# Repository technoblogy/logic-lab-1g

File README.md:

# Logic Lab 1G

A board that provides 12 logic gates that you can interconnect with patch cables to make a variety of different logic circuits. This version is implemented with 12 individual logic gates.

For more information see <http://www.technoblogy.com/show?4ODG>.

Alternatively see [Logic Lab](https://github.com/technoblogy/logic-lab) which is functionally identical, but implemented using an AVR microcontroller.

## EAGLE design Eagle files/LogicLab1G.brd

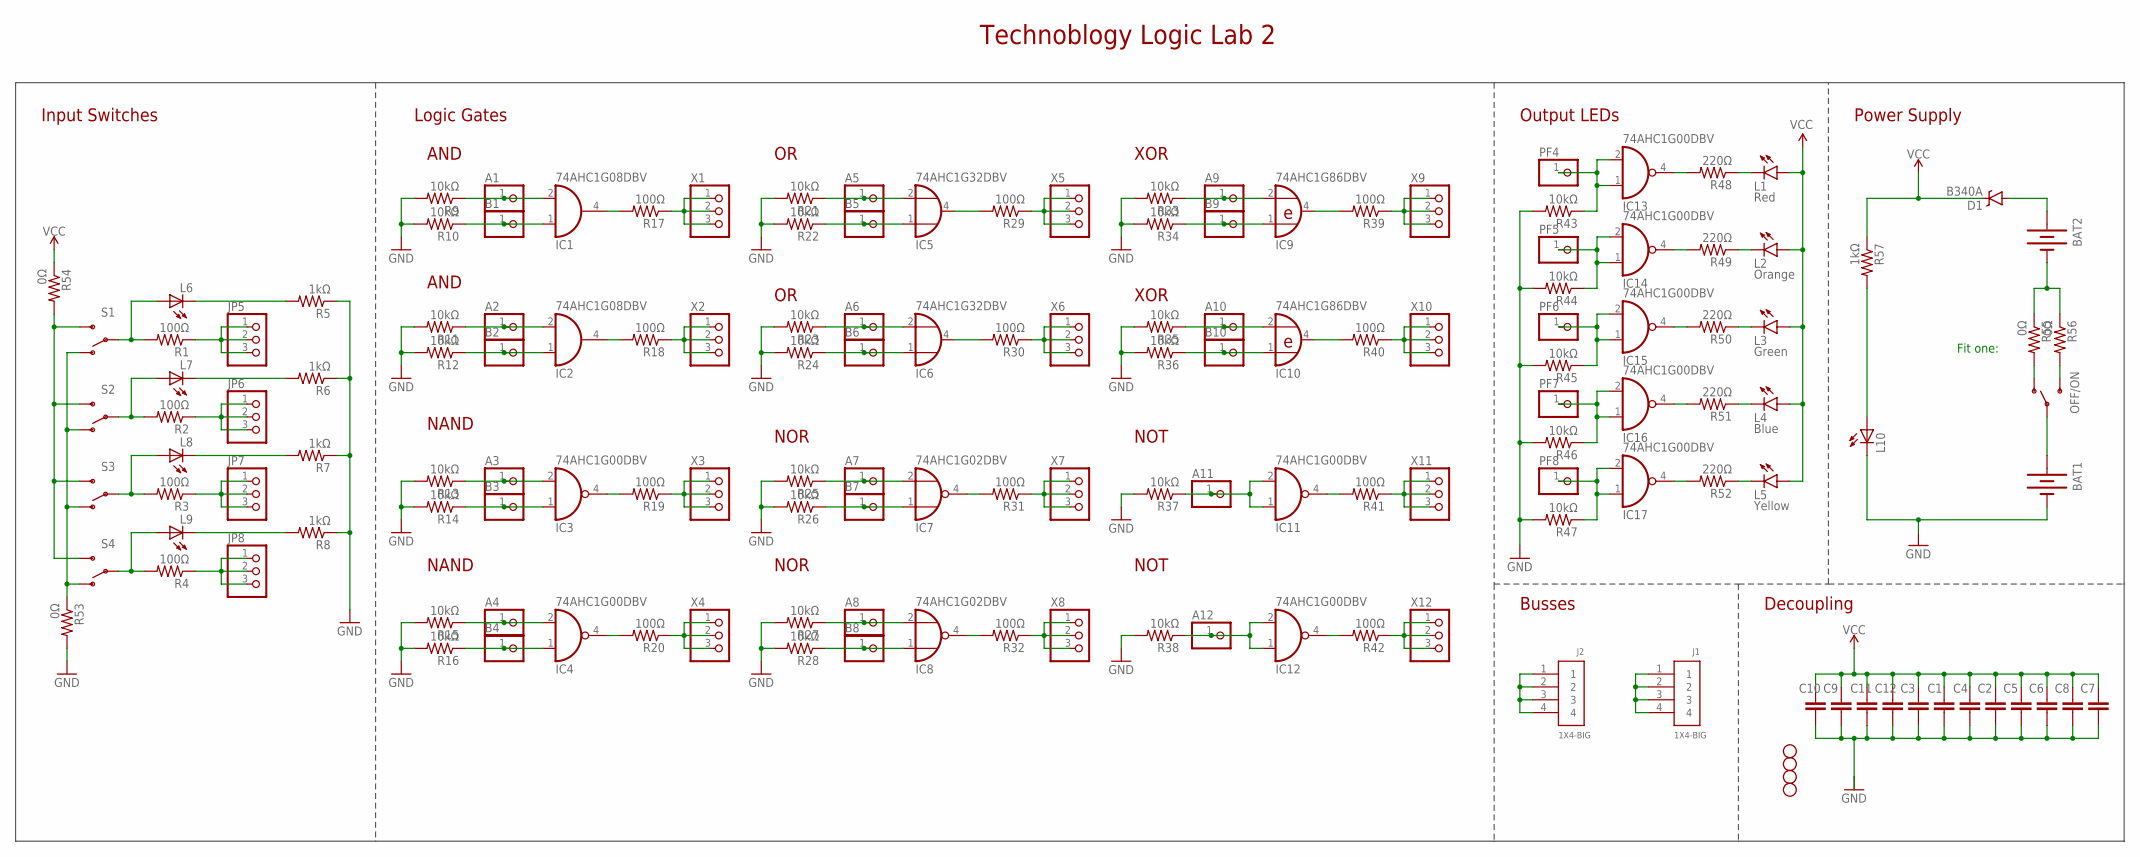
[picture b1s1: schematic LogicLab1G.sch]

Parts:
A1, A2, A3, A4, A5, A6, A7, A8, A9, A10, A11, A12: PINHD-1X1; 1X01
B1, B2, B3, B4, B5, B6, B7, B8, B9, B10: PINHD-1X1; 1X01
BAT1, BAT2: BATTERYAAA-KIT; BATTERY-AAA-KIT
C1, C2, C3, C5, C6, C7, C8, C9, C10, C12: 100n; 0805
C4, C11: 10uF; 0805
D1: B340A; SMA-DIODE
IC1, IC2: 74AHC1G08DBV; SOT23-5
IC3, IC4, IC11, IC12, IC13, IC14, IC15, IC16, IC17: 74AHC1G00DBV; SOT23-5
IC5, IC6: 74AHC1G32DBV; SOT23-5
IC7, IC8: 74AHC1G02DBV; SOT23-5
IC9, IC10: 74AHC1G86DBV; SOT23-5
J1, J2: 1X4-BIG; 1X04-BIG
JP1, JP2, JP3, JP4: STAND-OFF
JP5, JP6, JP7, JP8: PINHD-1X3; 1X03
L1: Red; LED5MM
L2: Orange; LED5MM
L3: Green; LED5MM
L4: Blue; LED5MM
L5: Yellow; LED5MM
L6, L7, L8, L9, L10: LEDCHIPLED_0805; CHIPLED_0805
OFF/ON: SWITCH-SPDTKIT; SWITCH-SPDT_KIT
PF4, PF5, PF6, PF7, PF8: PINHD-1X1; 1X01
R1, R2, R3, R4, R17, R18, R19, R20, R29, R30, R31, R32, R39, R40, R41, R42: 100Ω; 0805
R5, R6, R7, R8, R57: 1kΩ; 0805
R9, R10, R11, R12, R13, R14, R15, R16, R21, R22, R23, R24, R25, R26, R27, R28, R33, R34, R35, R36, R37, R38, R43, R44, R45, R46, R47: 10kΩ; 0805
R48, R49, R50, R51, R52: 220Ω; 0805
R53, R54, R55, R56: 0Ω; 0805
S1, S2, S3, S4: SWITCH-SPDTKIT; SWITCH-SPDT_KIT
X1, X2, X3, X4, X5, X6, X7, X8, X9, X10, X11, X12: PINHD-1X3; 1X03

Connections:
BOTTOMS: R53.1, S1.1 (O), S2.1 (O), S3.1 (O), S4.1 (O)
GND: BAT1.GND@1 (-), C1.2, C2.2, C3.2, C4.2, C5.2, C6.2, C7.2, C8.2, C9.2, C10.2, C11.2, C12.2, IC1.3 (GND), IC2.3 (GND), IC3.3 (GND), IC4.3 (GND), IC5.3 (GND), IC6.3 (GND), IC7.3 (GND), IC8.3 (GND), IC9.3 (GND), IC10.3 (GND), IC11.3 (GND), IC12.3 (GND), IC13.3 (GND), IC14.3 (GND), IC15.3 (GND), IC16.3 (GND), IC17.3 (GND), L10.C, R5.1, R6.1, R7.1, R8.1, R9.2, R10.2, R11.2, R12.2, R13.2, R14.2, R15.2, R16.2, R21.2, R22.2, R23.2, R24.2, R25.2, R26.2, R27.2, R28.2, R33.2, R34.2, R35.2, R36.2, R37.2, R38.2, R43.2, R44.2, R45.2, R46.2, R47.2, R53.2
unnamed: A9.1, IC9.2 (I1), R33.1
unnamed: R30.1, X6.1, X6.2, X6.3
unnamed: R29.1, X5.1, X5.2, X5.3
unnamed: B4.1, IC4.1 (I0), R16.1
unnamed: IC13.4 (O), R48.2
unnamed: IC14.4 (O), R49.2
unnamed: IC15.4 (O), R50.2
unnamed: BAT1.PWR@1 (+), OFF/ON.2
unnamed: B10.1, IC10.1 (I0), R36.1
unnamed: IC16.4 (O), R51.2
unnamed: A4.1, IC4.2 (I1), R15.1
unnamed: IC17.4 (O), R52.2
unnamed: BAT2.PWR@1 (+), D1.A
unnamed: R39.1, X9.1, X9.2, X9.3
unnamed: IC2.4 (O), R18.2
unnamed: OFF/ON.1 (O), R55.2
unnamed: R40.1, X10.1, X10.2, X10.3
unnamed: A1.1, IC1.2 (I1), R9.1
unnamed: IC5.4 (O), R29.2
unnamed: BAT2.GND@1 (-), R55.1, R56.1
unnamed: L1.K (C), R48.1
unnamed: B3.1, IC3.1 (I0), R14.1
unnamed: B1.1, IC1.1 (I0), R10.1
unnamed: B7.1, IC7.1 (I0), R26.1
unnamed: B9.1, IC9.1 (I0), R34.1
unnamed: R17.1, X1.1, X1.2, X1.3
unnamed: R41.1, X11.1, X11.2, X11.3
unnamed: OFF/ON.3 (S), R56.2
unnamed: R18.1, X2.1, X2.2, X2.3
unnamed: B2.1, IC2.1 (I0), R12.1
unnamed: A10.1, IC10.2 (I1), R35.1
unnamed: R42.1, X12.1, X12.2, X12.3
unnamed: L6.A, R1.2, S1.2
unnamed: R19.1, X3.1, X3.2, X3.3
unnamed: A8.1, IC8.2 (I1), R27.1
unnamed: R31.1, X7.1, X7.2, X7.3
unnamed: B5.1, IC5.1 (I0), R22.1
unnamed: L7.A, R2.2, S2.2
unnamed: A5.1, IC5.2 (I1), R21.1
unnamed: IC3.4 (O), R19.2
unnamed: IC9.4 (O), R39.2
unnamed: IC10.4 (O), R40.2
unnamed: IC12.4 (O), R42.2
unnamed: IC11.4 (O), R41.2
unnamed: R32.1, X8.1, X8.2, X8.3
unnamed: A11.1, IC11.1 (I0), IC11.2 (I1), R37.1
unnamed: A12.1, IC12.1 (I0), IC12.2 (I1), R38.1
unnamed: L2.K (C), R49.1
unnamed: IC6.4 (O), R30.2
unnamed: L8.A, R3.2, S3.2
unnamed: L9.A, R4.2, S4.2
unnamed: IC4.4 (O), R20.2
unnamed: R20.1, X4.1, X4.2, X4.3
unnamed: L3.K (C), R50.1
unnamed: L4.K (C), R51.1
unnamed: L5.K (C), R52.1
unnamed: IC13.1 (I0), IC13.2 (I1), PF4.1, R43.1
unnamed: IC14.1 (I0), IC14.2 (I1), PF5.1, R44.1
unnamed: JP8.1, JP8.2, JP8.3, R4.1
unnamed: JP7.1, JP7.2, JP7.3, R3.1
unnamed: L10.A, R57.2
unnamed: J2.1, J2.2, J2.3, J2.4
unnamed: JP6.1, JP6.2, JP6.3, R2.1
unnamed: L9.C, R8.2
unnamed: L8.C, R7.2
unnamed: JP5.1, JP5.2, JP5.3, R1.1
unnamed: L6.C, R5.2
unnamed: L7.C, R6.2
unnamed: B8.1, IC8.1 (I0), R28.1
unnamed: J1.1, J1.2, J1.3, J1.4
unnamed: A6.1, IC6.2 (I1), R23.1
unnamed: IC15.1 (I0), IC15.2 (I1), PF6.1, R45.1
unnamed: B6.1, IC6.1 (I0), R24.1
unnamed: A7.1, IC7.2 (I1), R25.1
unnamed: A3.1, IC3.2 (I1), R13.1
unnamed: A2.1, IC2.2 (I1), R11.1
unnamed: IC8.4 (O), R32.2
unnamed: IC7.4 (O), R31.2
unnamed: IC16.1 (I0), IC16.2 (I1), PF7.1, R46.1
unnamed: IC17.1 (I0), IC17.2 (I1), PF8.1, R47.1
unnamed: IC1.4 (O), R17.2
TOPS: R54.2, S1.3 (S), S2.3 (S), S3.3 (S), S4.3 (S)
VCC: C1.1, C2.1, C3.1, C4.1, C5.1, C6.1, C7.1, C8.1, C9.1, C10.1, C11.1, C12.1, D1.C, IC1.5 (VCC), IC2.5 (VCC), IC3.5 (VCC), IC4.5 (VCC), IC5.5 (VCC), IC6.5 (VCC), IC7.5 (VCC), IC8.5 (VCC), IC9.5 (VCC), IC10.5 (VCC), IC11.5 (VCC), IC12.5 (VCC), IC13.5 (VCC), IC14.5 (VCC), IC15.5 (VCC), IC16.5 (VCC), IC17.5 (VCC), L1.A, L2.A, L3.A, L4.A, L5.A, R54.1, R57.1

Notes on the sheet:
Technoblogy Logic Lab 2
Input Switches
Logic Gates
Output LEDs
Power Supply
AND
Busses
NAND
NOR
NOT
XOR
Decoupling
Fit one:

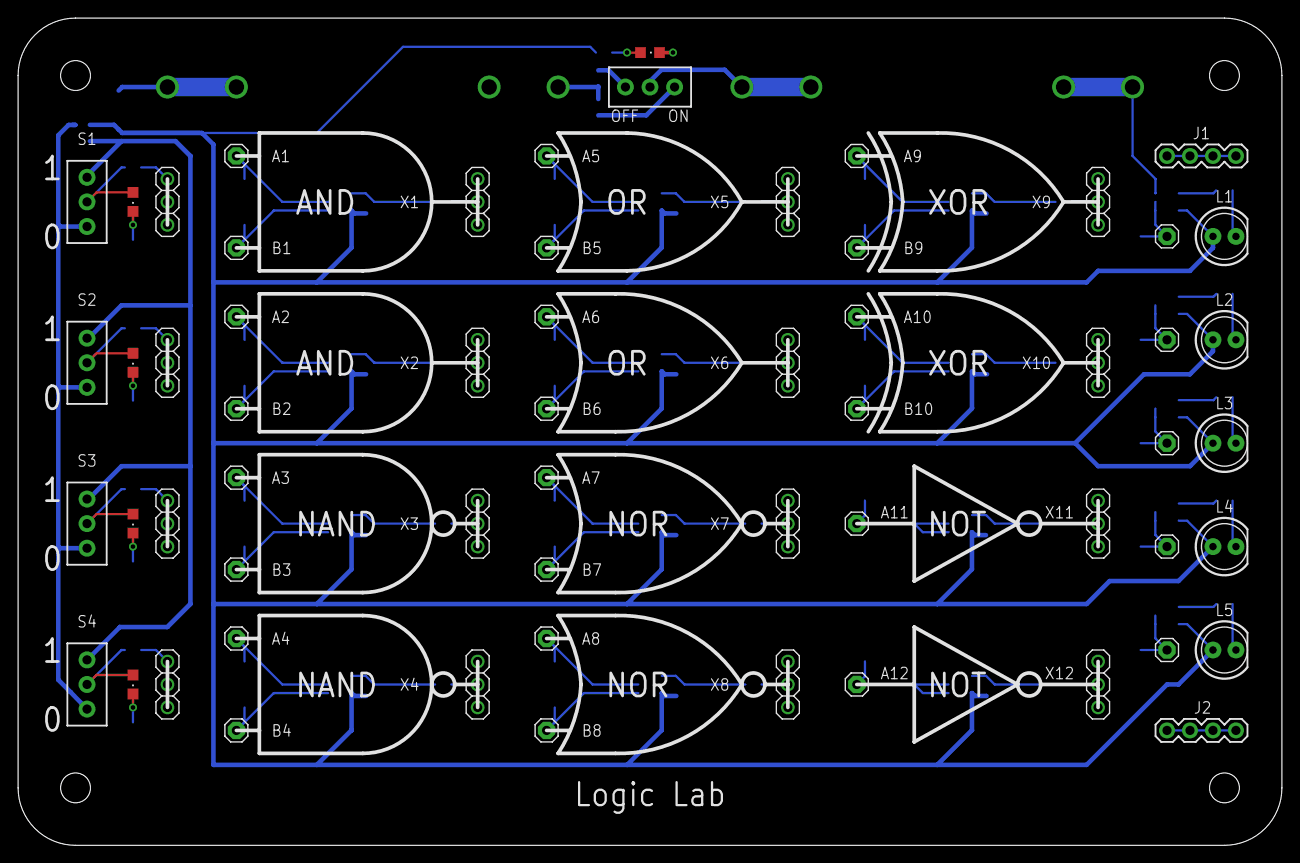
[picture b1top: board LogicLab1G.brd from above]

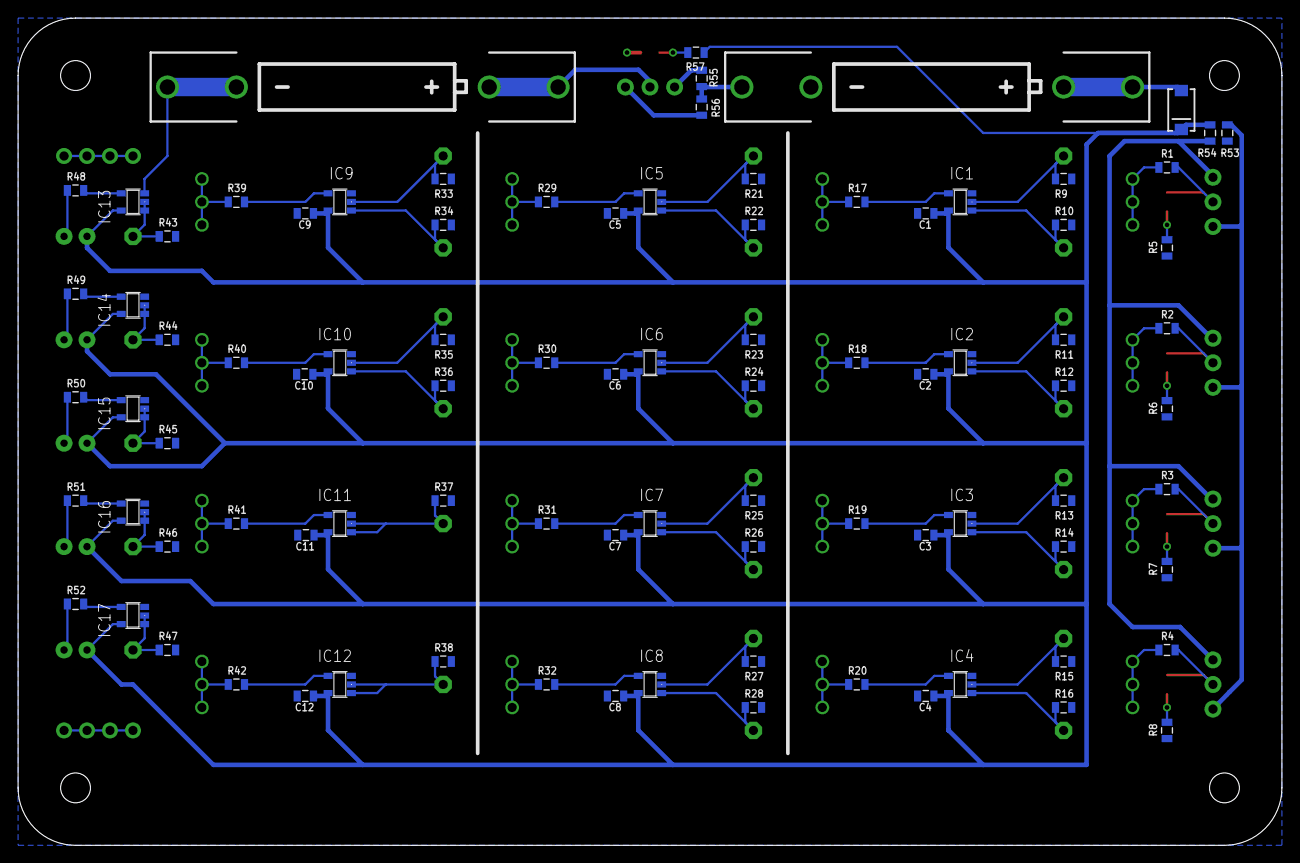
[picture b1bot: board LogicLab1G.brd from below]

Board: 2 copper layers, 139.7 x 91.4 mm, 153 parts (89 on the bottom side), 85 nets.

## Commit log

2024-05-05 Version 1 - 5th May 2024
2024-06-17 Version 1a - 17th June 2024
    Corrected the part numbers of the logic gates.
2026-02-28 CC BY-SA 4.0

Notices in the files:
parts and their libraries:
SparkFun-Electromechanical: Licensing: Creative Commons ShareAlike 4.0 International - https://creativecommons.org/licenses/by-sa/4.0
